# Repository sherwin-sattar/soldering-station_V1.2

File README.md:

# Soldering Station V1.2

## 3D views

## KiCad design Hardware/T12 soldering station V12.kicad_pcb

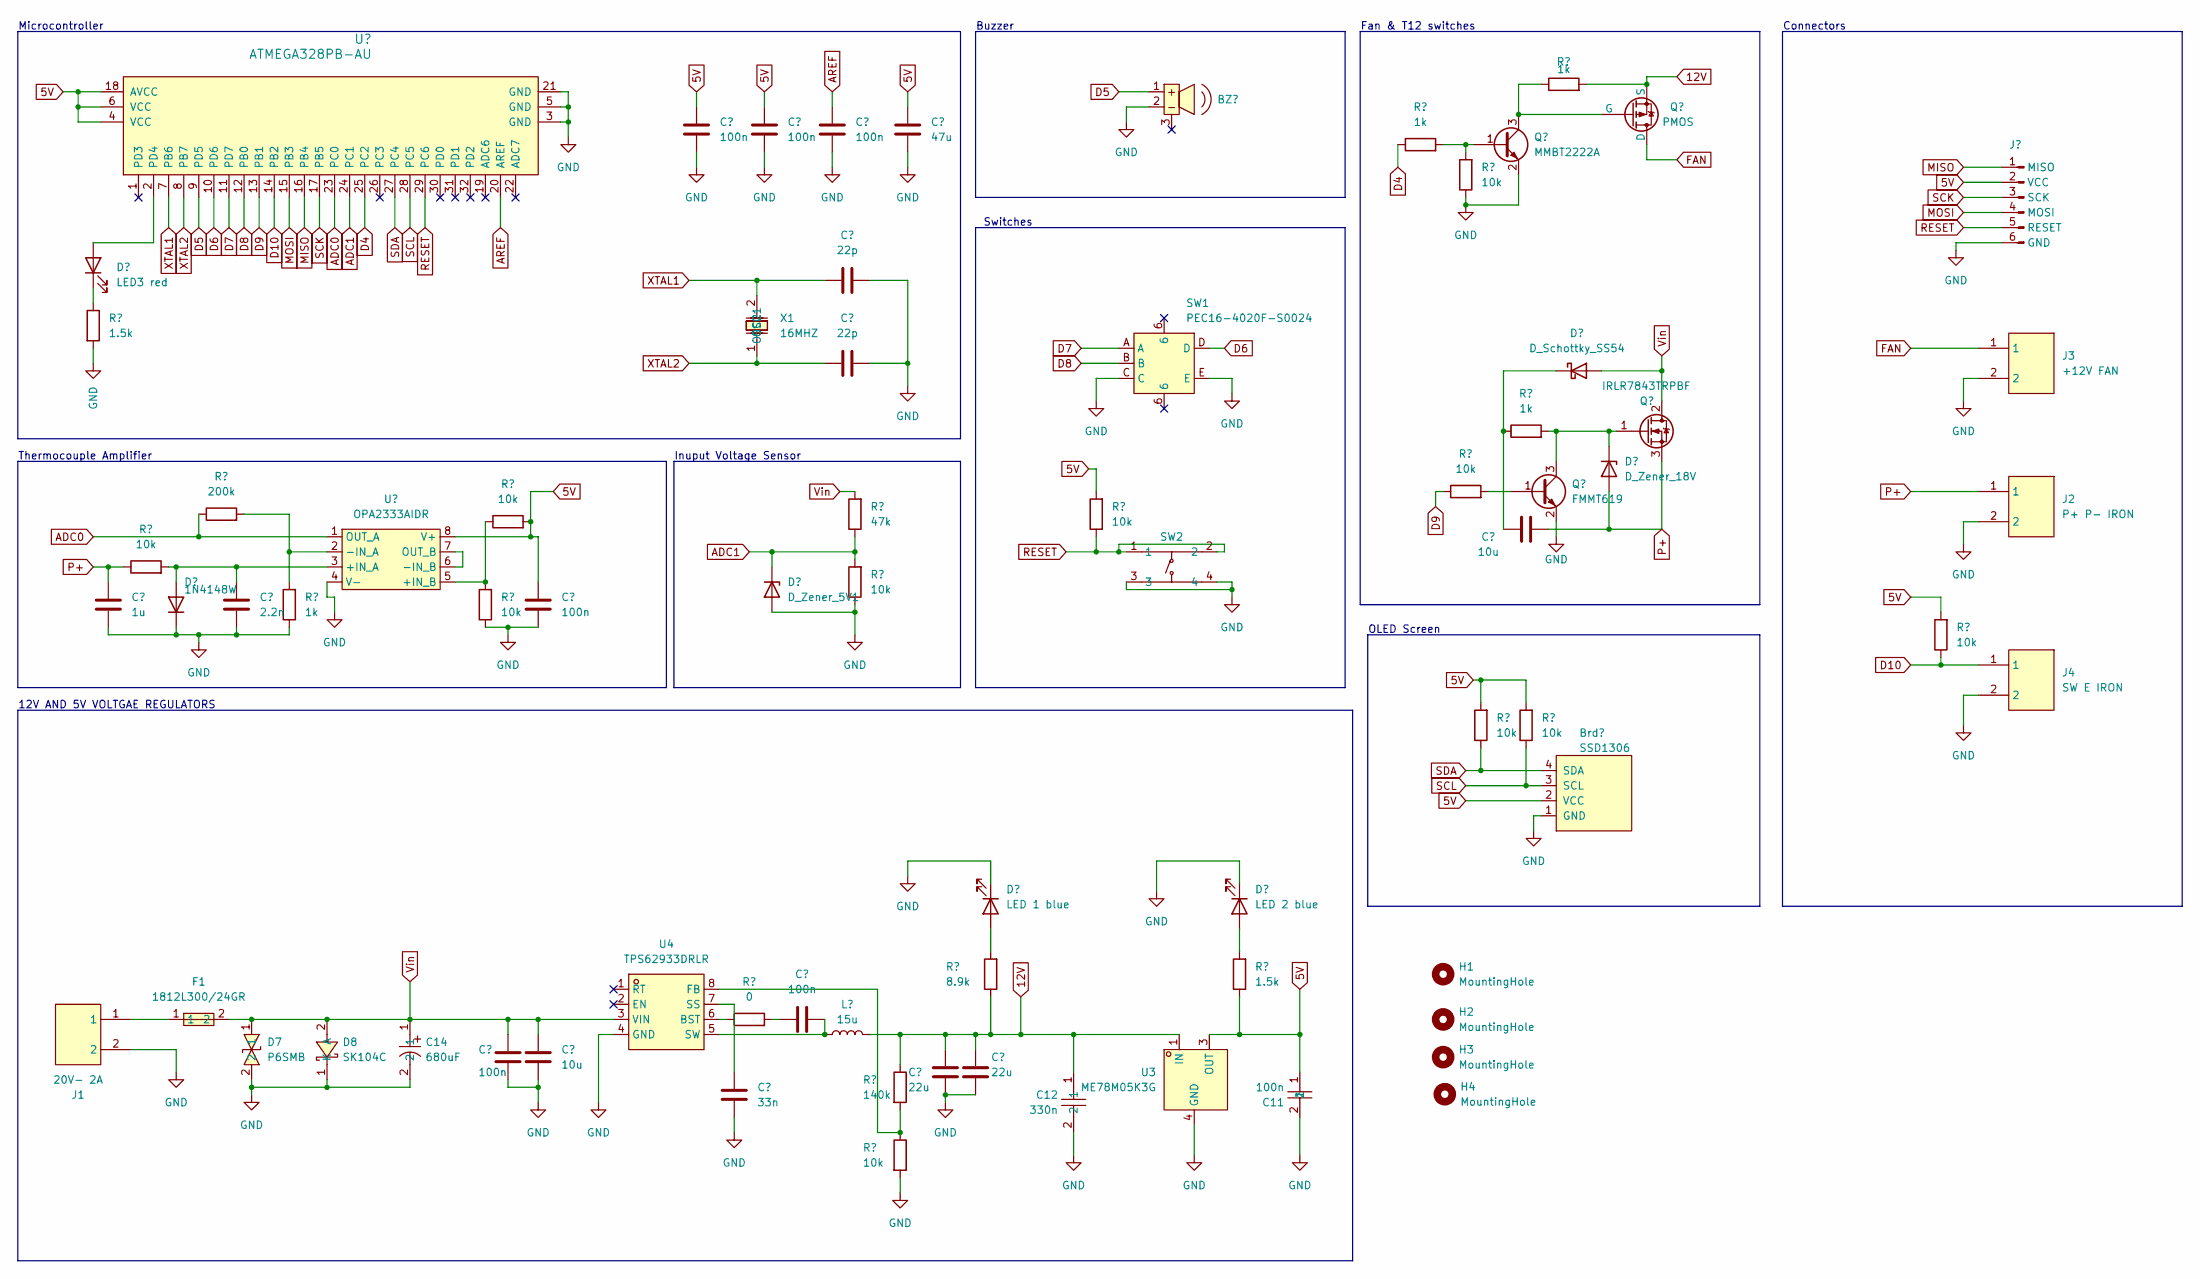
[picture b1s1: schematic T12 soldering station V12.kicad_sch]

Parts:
BZ1: Buzzer; LCSC PN C95297
C1, C2, C3, C9, C11, C13, C15: 100n; C_0603_1608Metric; LCSC PN C1590
C4: 47u; C_1206_3216Metric; LCSC PN C96123
C5, C6: 22p; C_0603_1608Metric; LCSC PN C1653
C7: 10u; C_1206_3216Metric; LCSC PN C92797
C8: 2.2n; C_0603_1608Metric; LCSC PN C16033
C10: 1u; C_0603_1608Metric; LCSC PN C15849
C12: 330n; C_0603_1608Metric; LCSC PN C694217
C14: 680uF; CAP-SMD_BD10.0-L10.3-W10.3-LS10.9-FD; LCSC PN C2980172
C16: 10u; C_1210_3225Metric; LCSC PN C1952589
C17: 33n; C_0603_1608Metric; LCSC PN C113810
C18, C19: 22u; C_1210_3225Metric; LCSC PN C21397
D1: D_Schottky_SS54; D_SMA; LCSC PN C123946
D2: D_Zener_18V; D_SOD-123; LCSC PN C116111
D3: D_Zener_5V1; D_SOD-123; LCSC PN C81601
D4: 1N4148W; D_SOD-123; LCSC PN C241939
D5: LED 1 blue; LED_0603_1608Metric; LCSC PN C965799
D6: LED 2 blue; LED_0603_1608Metric; LCSC PN C965799
D7: P6SMB; DO-214AA_L4.4-W3.6-LS5.3-BI; LCSC PN C776247
D8: SK104C; SMC_L6.9-W5.9-LS7.9-RD; LCSC PN C18199211
D9: LED3 red; LED_0603_1608Metric; LCSC PN C440519
F1: 1812L300/24GR; F1812; LCSC PN C20627123
H1, H2, H3, H4: MountingHole; MountingHole_2.7mm_Pad_TopBottom
J1: 20V- 2A; CONN-TH_2P-P5.00_WJ128V-5.0-2P; LCSC PN C8269
J2: P+ P- IRON; CONN-TH_2P-P5.00_WJ128V-5.0-2P; LCSC PN C8269
J3: +12V FAN; CONN-TH_2P-P5.00_WJ128V-5.0-2P; LCSC PN C8269
J4: SW E IRON; CONN-TH_2P-P5.00_WJ128V-5.0-2P; LCSC PN C8269
J5: ISP_1x6
L1: 15u; L_10.4x10.4_H4.8; LCSC PN C7245131
LCD1: SSD1306; oled0.96_4pin; LCSC PN C5248080
Q1: PMOS; SOT-23; LCSC PN C15127
Q2: MMBT2222A; SOT-23; LCSC PN C194252
Q3: IRLR7843TRPBF; TO-252-2; LCSC PN C21988
Q4: FMMT619; SOT-23; LCSC PN C53071
R1, R2, R11: 1k; R_0603_1608Metric; LCSC PN C21190
R3, R5, R8, R9, R10, R12, R13, R14, R15, R16, R22: 10k; R_0603_1608Metric; LCSC PN C25804
R4: 1k; R_1206_3216Metric; LCSC PN C4410
R6: 200k; R_0603_1608Metric; LCSC PN C25811
R7: 47k; R_0603_1608Metric; LCSC PN C25819
R17: 8.9k; R_0603_1608Metric; LCSC PN C5197519
R18, R23: 1.5k; R_0603_1608Metric; LCSC PN C22843
R20: 140k; R_0603_1608Metric; LCSC PN C844526
R21: 0; R_0603_1608Metric; LCSC PN C17168
SW1: PEC16-4020F-S0024; SW-TH_PEC16-4020F-S0024; LCSC PN C143803
SW2: PTS645SH50SMTR92LFS; KEY-SMD_4P-L6.0-W6.0-P4.50-LS9.0; LCSC PN C221869
U1: ATMEGA328PB-AU; TQFP-32_7x7mm; MPN ATMEGA328P-AU; Digi-Key_PN ATMEGA328P-AU-ND
U2: OPA2333AIDR; SOIC-8_3.9x4.9mm_P1.27mm; LCSC PN C38732
U3: ME78M05K3G; TO-252-2_L6.5-W6.1-P4.58-LS10.0-TL; LCSC PN C83969
U4: TPS62933DRLR; SOT-583-8_L2.1-W1.2-P0.50-LS1.6-BR; LCSC PN C3200405
X1: 16MHZ; OSC-SMD_L5.0-W3.2; LCSC PN C112572

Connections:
5V: C1.2, C2.2, C4.2, C9.2, C11.1, J5.2 (VCC), LCD1.2 (VCC), R8.2, R13.2, R14.2, R15.2, R16.2, R18.1, U1.4 (VCC), U1.6 (VCC), U1.18 (AVCC), U2.8 (V+), U3.3 (OUT)
12V: C12.1, C18.1, C19.1, L1.2, Q1.2 (S), R1.2, R17.1, R20.1, U3.1 (IN)
ADC0: R6.1, U1.23 (PC0), U2.1 (OUT_A)
ADC1: D3.1 (K), R7.1, R10.2, U1.24 (PC1)
AREF: C3.2, U1.20 (AREF)
D4: R2.1, U1.25 (PC2)
D5: BZ1.1, U1.9 (PD5)
D6: SW1.D, U1.10 (PD6)
D7: SW1.A, U1.11 (PD7)
D8: SW1.B, U1.12 (PB0)
D9: R5.1, U1.13 (PB1)
D10: J4.1, R13.1, U1.14 (PB2)
FAN: J3.1, Q1.3 (D)
GND: BZ1.2, C1.1, C2.1, C3.1, C4.1, C5.1, C6.1, C8.1, C9.1, C10.1, C11.2, C12.2, C14.2, C15.2, C16.2, C17.2, C18.2, C19.2, D3.2 (A), D4.1 (K), D5.1 (K), D6.1 (K), D7.2, D8.1 (K), J1.2, J2.2, J3.2, J4.2, J5.6 (GND), LCD1.1 (GND), Q2.2 (E), Q4.2 (E), R3.1, R10.1, R11.1, R12.1, R22.2, R23.2, SW1.C, SW1.E, SW2.3, SW2.4, U1.3 (GND), U1.5 (GND), U1.21 (GND), U2.4 (V-), U3.4 (GND), U4.4 (GND)
MISO: J5.1 (MISO), U1.16 (PB4)
MOSI: J5.4 (MOSI), U1.15 (PB3)
unnamed: C13.1, R21.2
unnamed: C7.1, D1.1 (K), R4.1
unnamed: D2.1 (K), Q3.1 (G), Q4.3 (C), R4.2
unnamed: C8.2, D4.2 (A), R9.2, U2.3 (+IN_A)
unnamed: D5.2 (A), R17.2
unnamed: D6.2 (A), R18.2
unnamed: D9.2 (A), U1.2 (PD4)
unnamed: D9.1 (K), R23.1
unnamed: F1.1, J1.1
unnamed: Q1.1 (G), Q2.3 (C), R1.1
unnamed: Q2.1 (B), R2.2, R3.2
unnamed: Q4.1 (B), R5.2
unnamed: R8.1, R12.2, U2.5 (+IN_B)
unnamed: R6.2, R11.2, U2.2 (-IN_A)
unnamed: U2.6 (-IN_B), U2.7 (OUT_B)
unnamed: R21.1, U4.6 (BST)
unnamed: R20.2, R22.1, U4.8 (FB)
unnamed: C17.1, U4.7 (SS)
unnamed: C13.2, L1.1, U4.5 (SW)
P+: C7.2, C10.2, D2.2 (A), J2.1, Q3.3 (S), R9.1
RESET: J5.5 (RESET), R16.1, SW2.1, SW2.2, U1.29 (PC6)
SCK: J5.3 (SCK), U1.17 (PB5)
SCL: LCD1.3 (SCL), R15.1, U1.28 (PC5)
SDA: LCD1.4 (SDA), R14.1, U1.27 (PC4)
Vin: C14.1, C15.1, C16.1, D1.2 (A), D7.1, D8.2 (A), F1.2, Q3.2 (D), R7.2, U4.3 (VIN)
XTAL1: C5.2, U1.7 (PB6), X1.2 (OSC2)
XTAL2: C6.2, U1.8 (PB7), X1.1 (OSC1)

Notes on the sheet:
Fan & T12 switches
OLED Screen
Inuput Voltage Sensor
12V AND 5V VOLTGAE REGULATORS
Thermocouple Amplifier
Switches
Microcontroller
Connectors
Buzzer

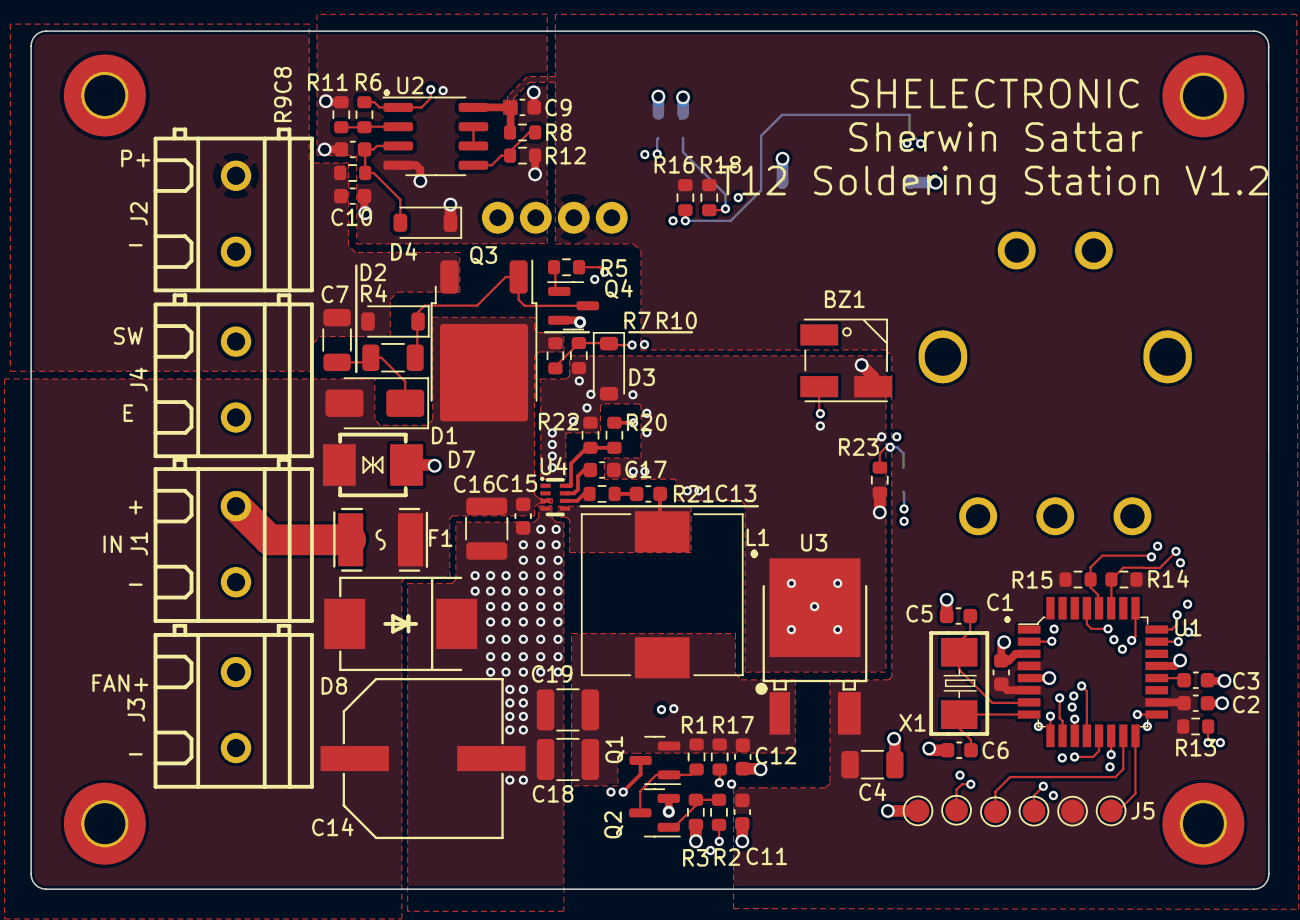
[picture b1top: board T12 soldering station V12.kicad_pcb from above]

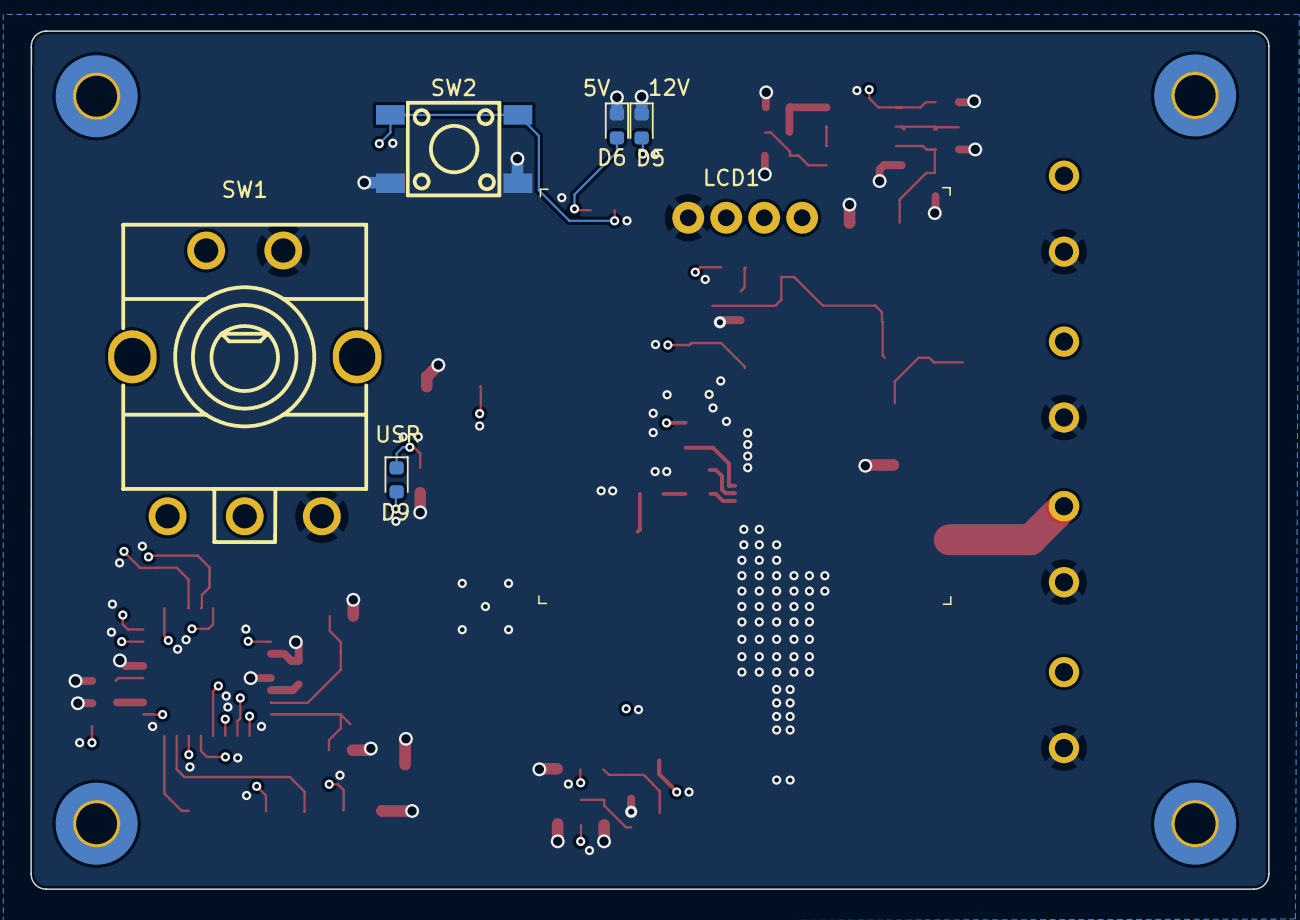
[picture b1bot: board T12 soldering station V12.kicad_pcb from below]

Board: 4 copper layers, 81.5 x 56.5 mm, 74 parts (6 on the bottom side), 43 nets.
